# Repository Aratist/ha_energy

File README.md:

# Gestionnaire d'énergie solaire pour Home Assistant

Intégration personnalisée (`custom_components/energy_manager`) qui minimise le coût de
l'électricité d'une maison équipée de panneaux solaires et d'un abonnement heures
pleines / heures creuses : elle oriente le solaire vers le chauffe-eau, la pompe de
piscine et la clim/chauffage, reporte en heures creuses ce qui n'est pas rentable en
journée, et maintient la maison dans une bande de confort.

Elle ne parle à aucun matériel directement : elle s'appuie sur les entités que vous avez
déjà dans Home Assistant (compteur Linky/pince, onduleur, prises ou relais, thermostat).

## Installation

Via HACS (recommandé) :

1. *HACS → ⋮ → Dépôts personnalisés*, ajouter `https://github.com/Aratist/ha_energy`
   avec le type *Intégration*.
2. Rechercher *Gestionnaire d'énergie solaire* dans HACS, puis *Télécharger*.
3. Redémarrer Home Assistant.
4. *Paramètres → Appareils et services → Ajouter une intégration → Gestionnaire d'énergie solaire*.

Manuellement : copier `custom_components/energy_manager` dans `config/custom_components/`,
puis reprendre à l'étape 3.

Home Assistant 2024.12 ou plus récent est requis.

## Configuration

| Étape | Ce qu'il faut fournir |
|---|---|
| Mesures | Puissance réseau (> 0 en soutirage, < 0 en injection ; option d'inversion), consommation de la maison, production solaire, et le **talon** de consommation utilisé pour l'estimation |
| Équipements | Interrupteurs du chauffe-eau et de la pompe, entité `climate`, capteurs de puissance, sonde de piscine, température intérieure (optionnels) |
| Appareils | Liste libre d'appareils : entité qui dit s'il est allumé + puissance habituelle, et/ou capteur de puissance |
| Tarifs | Prix HP, HC et revente ; capteurs de prix optionnels (Tempo…) ; plage d'heures creuses |
| Confort | Bande hiver (19–23 °C par défaut) et bande été (24–27 °C) |
| Réglages | Puissances nominales, durées garanties, marge, hystérésis, durées min. marche/arrêt |

Tout est modifiable ensuite via le bouton **Configurer** de l'intégration.

## Fonctionnement

Toutes les 30 s :

1. **Mesures.** La consommation est celle du capteur si elle est disponible ; sinon elle est
   **estimée** = talon + appareils déclarés (mesurés ou puissance habituelle s'ils sont
   allumés) + équipements pilotés. La puissance réseau est mesurée, sinon déduite
   (consommation − production). Un capteur Linky indisponible n'arrête donc pas le pilotage.
2. **Rentabilité.** En heures pleines, un appareil différable (chauffe-eau, piscine) ne
   démarre que si le solaire couvre au moins `(HP − HC) / (HP − revente)` de sa puissance :
   au-delà, le faire tourner maintenant coûte moins cher que de l'attendre en heures creuses.
   Ce qui n'a pas pu tourner en journée est rattrapé pendant les heures creuses.
3. **Priorités selon la saison.** Hiver (novembre à mars, ou forcé via le sélecteur *Saison*) :
   chauffage > chauffe-eau > piscine. Été : chauffe-eau > piscine > clim.
4. **Confort.** En hiver, la consigne du chauffage est maintenue dans la bande ; quand le
   solaire couvre entièrement la puissance de la clim, la consigne monte au maximum de la
   bande pour stocker de la chaleur avant la soirée en heures pleines. En été, même principe
   inversé (la clim descend au minimum de la bande sur surplus). Une consigne changée à la
   main pendant un boost est respectée ; une clim éteinte n'est jamais rallumée.
5. **Chauffe-eau** : avec un capteur de puissance, une consommation nulle pendant 10 min
   alors qu'il est alimenté signifie « ballon chaud » ; en heures creuses ce signal est
   ignoré (le ballon a pu être vidé le soir, et le thermostat ne chauffe pas pour rien). **Piscine** : durée de filtration =
   température de l'eau / 2 (bornée), ou durée fixe sans sonde.
6. **Anti court-cycle** : durées minimales de marche/arrêt, et un équipement en marche n'est
   coupé que si le soutirage dépasse le seuil toléré.

Le cycle journalier commence à la fin des heures creuses.

## Entités créées

- **Mesures** : consommation (attribut `source` : mesurée/estimée), production, puissance
  réseau, puissance disponible, consommation des appareils, un capteur de puissance par
  appareil déclaré, température intérieure.
- **Tarifs** : tarif actuel (HP/HC), prix actuel, part solaire minimale rentable.
- **Bilan du jour** : soutirage, injection, autoconsommation (kWh), coût réseau et économie
  solaire (€). Remis à zéro à la fin des heures creuses. L'économie solaire est aussi
  cumulée par semaine, mois et année (attribut `period_start`), remise à zéro le lundi,
  le 1er du mois et le 1er janvier (calendrier local).
- **Pilotage** : état de chaque équipement (solaire, marche forcée, confort, terminé, en
  attente…), durées de chauffe / filtration, saison active.
- **Commandes** : sélecteur *Saison* (automatique / hiver / été), interrupteur *Pilotage
  automatique* (global) et un interrupteur *Gestion …* par équipement (piscine, clim,
  chauffe-eau) : coupé, l'équipement n'est plus du tout touché, par exemple pour garder le
  chauffage en télétravail ou piloter la pompe à la main pendant une vidange.

## Tableau de bord

Un tableau de bord prêt à coller (cartes natives uniquement) est fourni dans
[examples/dashboard.yaml](examples/dashboard.yaml).
Adaptez les entités indiquées en tête du fichier.

## Tests

La logique de décision (`engine.py`) est indépendante de Home Assistant :

```bash
python -m pytest tests
```

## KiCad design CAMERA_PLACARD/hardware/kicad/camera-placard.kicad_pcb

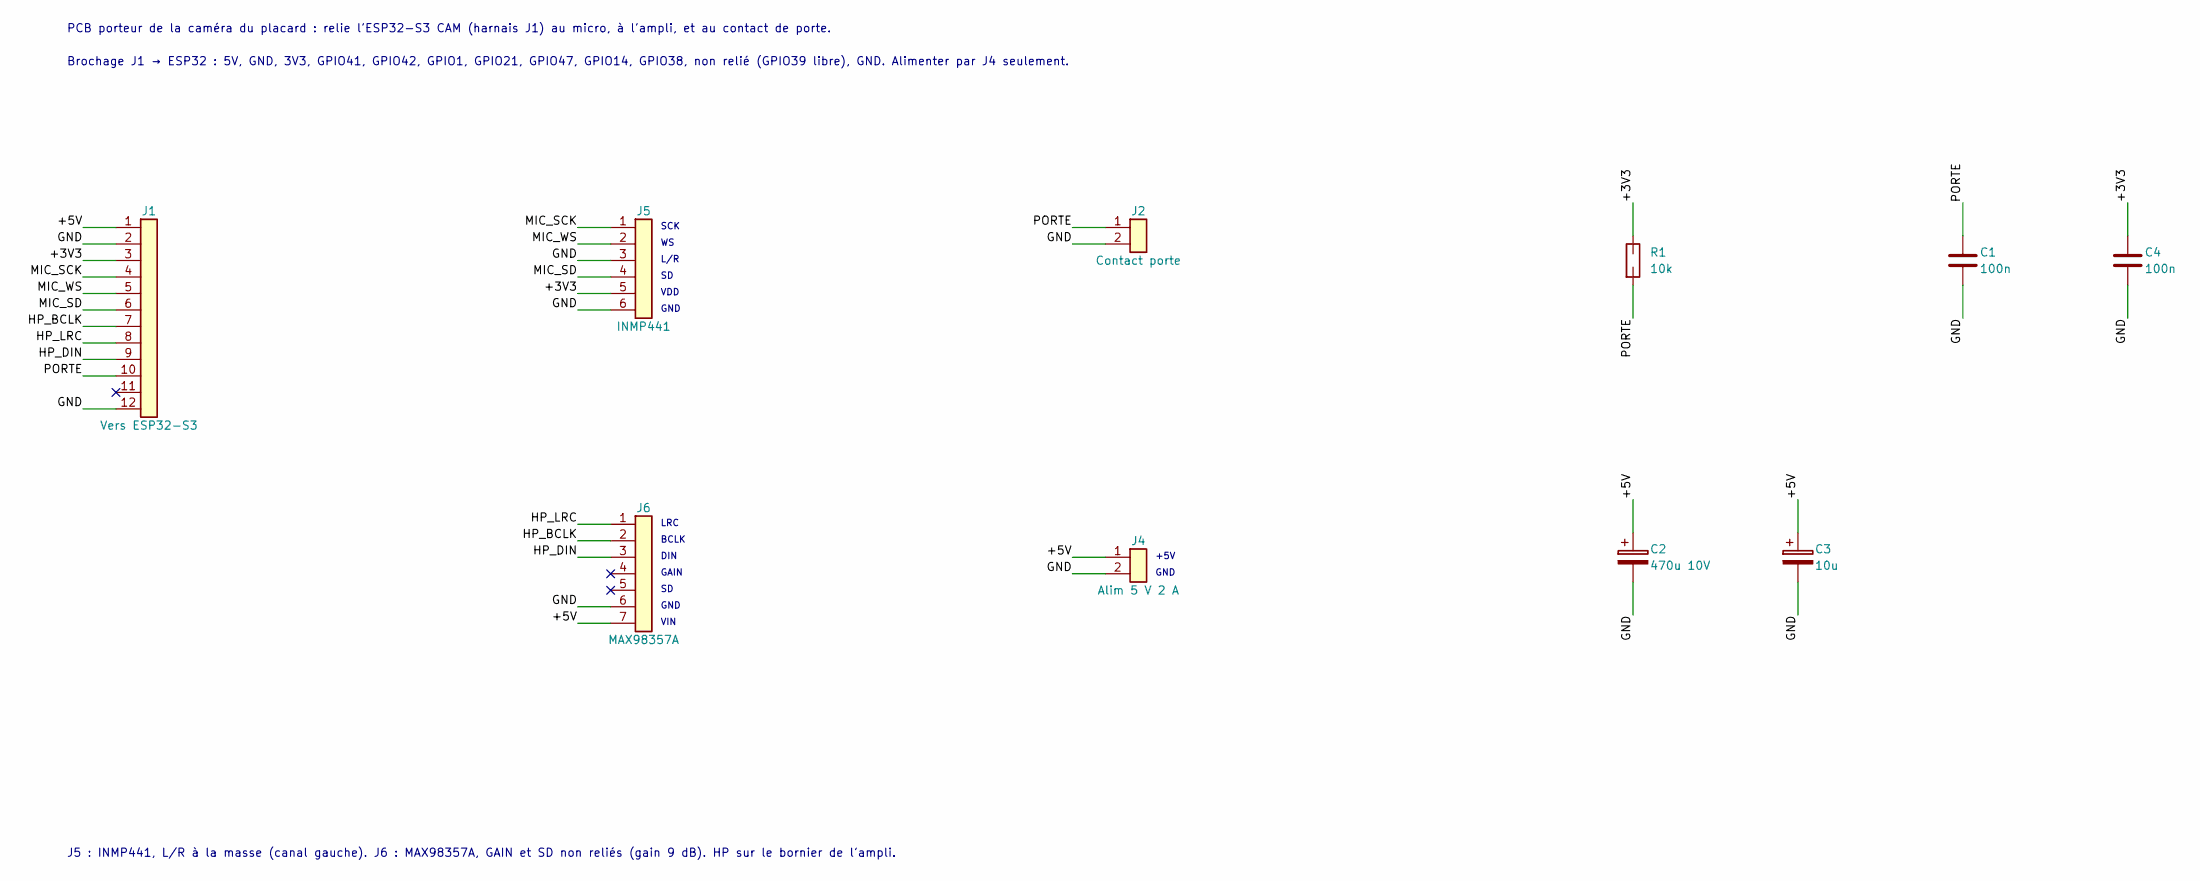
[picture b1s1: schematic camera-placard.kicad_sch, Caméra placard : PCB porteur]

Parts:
C1, C4: 100n; C_Disc_D5.0mm_W2.5mm_P5.00mm
C2: 470u 10V; CP_Radial_D10.0mm_P5.00mm
C3: 10u; CP_Radial_D5.0mm_P2.50mm
J1: Vers ESP32-S3; PinHeader_1x12_P2.54mm_Vertical
J2: Contact porte; JST_XH_B2B-XH-A_1x02_P2.50mm_Vertical
J4: Alim 5 V 2 A; TerminalBlock_Phoenix_MKDS-1,5-2-5.08_1x02_P5.08mm_Horizont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
J5: INMP441; PinSocket_1x06_P2.54mm_Vertical
J6: MAX98357A; PinSocket_1x07_P2.54mm_Vertical
R1: 10k; R_Axial_DIN0207_L6.3mm_D2.5mm_P10.16mm_Horizontal

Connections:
+3V3: C4.1, J1.3, J5.5, R1.1
+5V: C2.1, C3.1, J1.1, J4.1, J6.7
GND: C1.2, C2.2, C3.2, C4.2, J1.2, J1.12, J2.2, J4.2, J5.3, J5.6, J6.6
HP_BCLK: J1.7, J6.2
HP_DIN: J1.9, J6.3
HP_LRC: J1.8, J6.1
MIC_SCK: J1.4, J5.1
MIC_SD: J1.6, J5.4
MIC_WS: J1.5, J5.2
PORTE: C1.1, J1.10, J2.1, R1.2

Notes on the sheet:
SCK
L/R
VDD
GND
LRC
BCLK
DIN
GAIN
VIN
+5V
PCB porteur de la caméra du placard : relie l'ESP32-S3 CAM (harnais J1) au micro, à l'ampli, et au contact de porte.
Brochage J1 → ESP32 : 5V, GND, 3V3, GPIO41, GPIO42, GPIO1, GPIO21, GPIO47, GPIO14, GPIO38, non relié (GPIO39 libre), GND. Alimenter par J4 seulement.
J5 : INMP441, L/R à la masse (canal gauche). J6 : MAX98357A, GAIN et SD non reliés (gain 9 dB). HP sur le bornier de l'ampli.

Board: 2 copper layers, 14 parts (0 on the bottom side), 10 nets, no tracks yet.

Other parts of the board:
H1, H2, H3, H4: M2.5; MountingHole_2.7mm_M2.5

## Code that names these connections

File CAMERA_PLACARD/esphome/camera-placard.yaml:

# ESP32-S3 caméra du placard : caméra, micro I2S, haut-parleur I2S, contact de porte.
# Projet complet (câblage, scénario, boîtier, PCB) : CAMERA_PLACARD/CAMERA_PLACARD.md.
#
# Carte supposée : ESP32-S3 « CAM » au brochage caméra ESP32-S3-EYE (Freenove ESP32-S3 WROOM CAM,
# clones « ESP32-S3-CAM N8R8/N16R8 »), capteur OV2640 ou OV5640, PSRAM octale.
# Autre carte : changer les broches dans substitutions.
#
# Ne pas insérer de carte microSD : GPIO38 est l'une de ses broches sur la carte Freenove.
#
# À renseigner dans le secrets.yaml d'ESPHome : placard_api_key, placard_ota_password.
# Wi-Fi : point d'accès « Placard Fallback » au premier démarrage, comme le relais Madoka.

substitutions:
  flash_size: 8MB          # 16MB pour une carte N16R8.

  # Caméra (brochage ESP32-S3-EYE).
  cam_xclk: GPIO15
  cam_sda: GPIO4
  cam_scl: GPIO5
  cam_vsync: GPIO6
  cam_href: GPIO7
  cam_pclk: GPIO13

  # Micro INMP441.
  micro_bclk: GPIO41
  micro_ws: GPIO42
  micro_sd: GPIO1

  # Ampli MAX98357A.
  hp_bclk: GPIO21
  hp_lrc: GPIO47
  hp_din: GPIO14

  # Contact de porte (ILS).
  porte_pin: GPIO38

esphome:
  name: camera-placard
  friendly_name: Caméra placard
  min_version: 2025.5.0

esp32:
  board: esp32-s3-devkitc-1
  variant: esp32s3
  flash_size: ${flash_size}
  framework:
    type: esp-idf

psram:
  mode: octal
  speed: 80MHz

logger:

api:
  encryption:
    key: !secret placard_api_key

ota:
  - platform: esphome
    password: !secret placard_ota_password

wifi:
  ap:
    ssid: "Placard Fallback"
  # Le Wi-Fi en économie d'énergie hache l'audio et la vidéo.
  power_save_mode: none

captive_portal:

web_server:
  port: 80
  version: 3

# Bus SCCB de la caméra.
i2c:
  - id: bus_camera
    sda: ${cam_sda}
    scl: ${cam_scl}

esp32_camera:
  id: camera_placard
  name: Caméra
  external_clock:
    pin: ${cam_xclk}
    frequency: 20MHz
  i2c_id: bus_camera
  data_pins: [GPIO11, GPIO9, GPIO8, GPIO10, GPIO12, GPIO18, GPIO17, GPIO16]
  vsync_pin: ${cam_vsync}
  href_pin: ${cam_href}
  pixel_clock_pin: ${cam_pclk}
  # 800x600 suffit à la reconnaissance de visage à moins d'un mètre.
  resolution: 800x600
  jpeg_quality: 12
  max_framerate: 5 fps
  # Hors ouverture du placard, la caméra n'envoie presque rien.
  idle_framerate: 0.05 fps
  # À ajuster selon le sens de montage de la caméra dans le boîtier.
  vertical_flip: true
  horizontal_mirror: true

i2s_audio:
  - id: i2s_micro
    i2s_bclk_pin: ${micro_bclk}
    i2s_lrclk_pin: ${micro_ws}
  - id: i2s_hp
    i2s_bclk_pin: ${hp_bclk}
    i2s_lrclk_pin: ${hp_lrc}

microphone:
  - platform: i2s_audio
    id: micro
    i2s_audio_id: i2s_micro
    i2s_din_pin: ${micro_sd}
    adc_type: external
    pdm: false
    # Broche L/R de l'INMP441 reliée à la masse : canal gauche.
    channel: left
    bits_per_sample: 32bit

speaker:
  - platform: i2s_audio
    id: hp
    i2s_audio_id: i2s_hp
    i2s_dout_pin: ${hp_din}
    dac_type: external
    channel: mono
    sample_rate: 48000
    bits_per_sample: 16bit

media_player:
  - platform: speaker
    id: lecteur
    name: Haut-parleur
    volume_initial: 0.7
    announcement_pipeline:
      speaker: hp
      format: FLAC
      num_channels: 1
      sample_rate: 48000

# Le micro n'écoute le mot d'activation « Okay Nabu » que porte ouverte.
micro_wake_word:
  id: mot_activation
  microphone: micro
  models:
    - model: okay_nabu
  on_wake_word_detected:
    - voice_assistant.start:
        wake_word: !lambda return wake_word;

voice_assistant:
  id: assistant
  microphone: micro
  media_player: lecteur
  noise_suppression_level: 2
  auto_gain: 31dBFS
  volume_multiplier: 2.0
  on_end:
    - if:
        condition:
          binary_sensor.is_on: porte
        then:
          - micro_wake_word.start:

binary_sensor:
  # Contact magnétique : fermé (aimant présent) quand la porte est fermée.
  # Porte ouverte : contact ouvert, l'entrée remonte à 3,3 V par le pull-up.
  - platform: gpio
    id: porte
    name: Porte
    device_class: door
    pin:
      number: ${porte_pin}
      mode:
        input: true
        pullup: true
    filters:
      - delayed_on: 50ms
      - delayed_off: 500ms
    on_press:
      - micro_wake_word.start:
    on_release:
      - micro_wake_word.stop:
      - voice_assistant.stop:

sensor:
  - platform: wifi_signal
    name: Signal Wi-Fi
    update_interval: 60s
